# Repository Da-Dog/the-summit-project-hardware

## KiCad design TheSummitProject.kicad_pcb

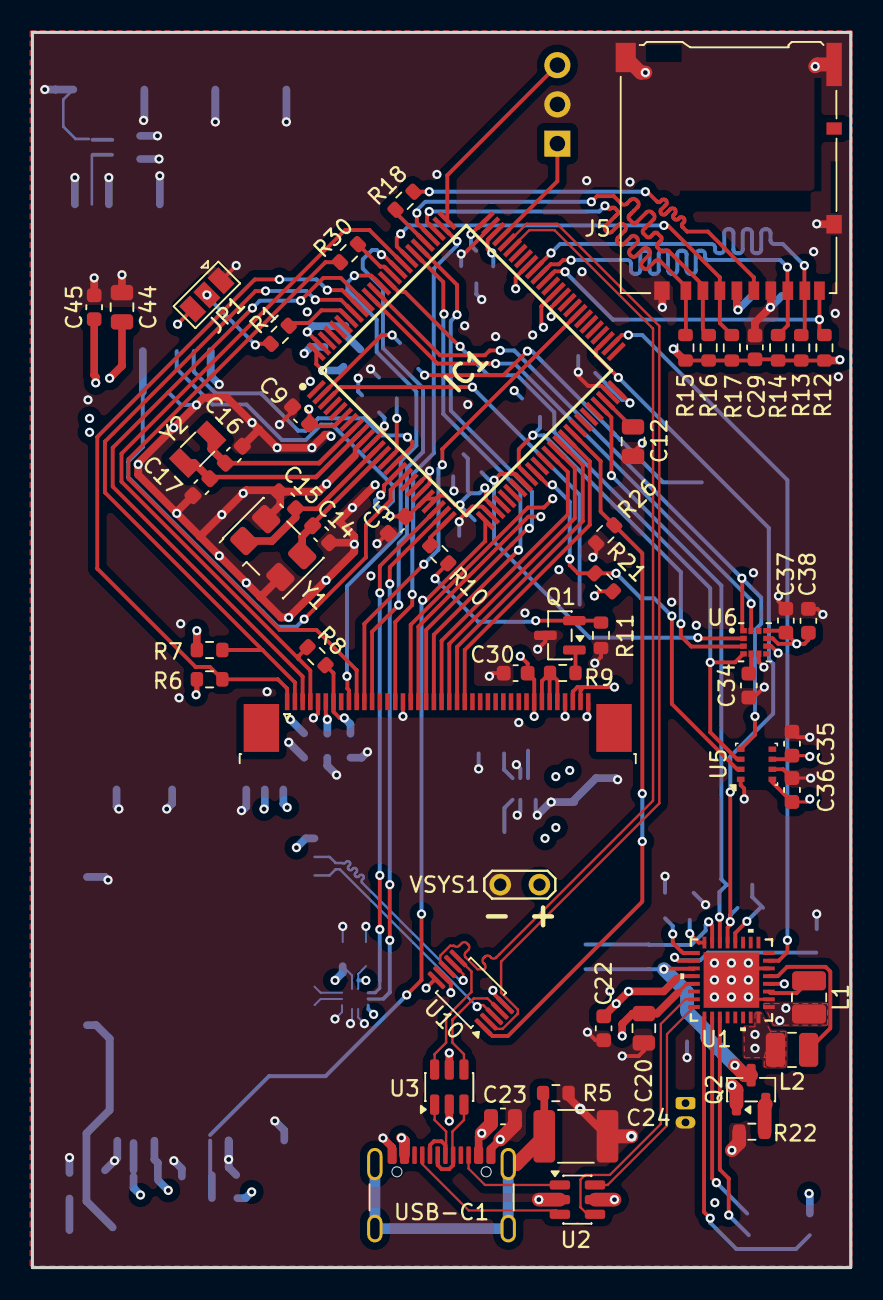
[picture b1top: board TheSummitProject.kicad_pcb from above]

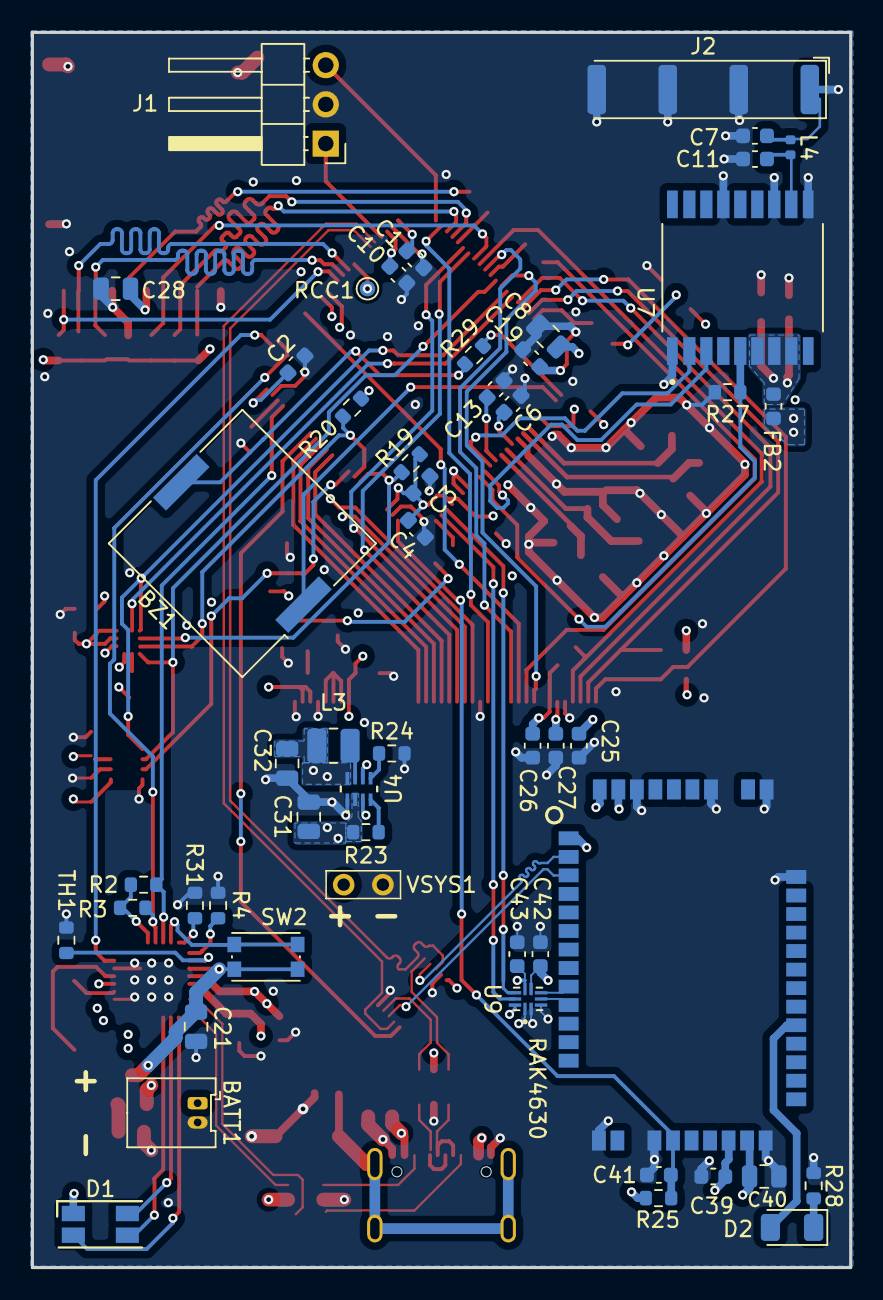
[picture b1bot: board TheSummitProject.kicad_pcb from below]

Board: 6 copper layers, 53.0 x 80.0 mm, 108 parts (51 on the bottom side), 100 nets.

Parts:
BATT1: Battery Connector; Molex_PicoBlade_53048-0210_1x02_P1.25mm_Horizontal
BZ1: PKLCS1212E4001-R1; Buzzer_Murata_PKLCS1212E
C1, C2, C3, C4, C5, C6, C9, C10, C13, C19, C23, C25, C26, C29, C30, C35, C36, C37, C38, C39, C41, C42, C43, C45: 100n; C_0603_1608Metric
C7: X; C_0603_1608Metric
C8, C28, C32, C40, C44: 10u; C_0805_2012Metric
C11: 1.8p; C_0603_1608Metric
C12, C20, C21, C31: 4.7u; C_0805_2012Metric
C14, C15: 10p; C_0603_1608Metric
C16, C17: 8p; C_0603_1608Metric
C22: 10u; C_0603_1608Metric
C24: 4.7n; C_1812_4532Metric
C27: 1u; C_0603_1608Metric
C34: 220n; C_0603_1608Metric
D1: PWR_LED; LED_RGB_1210
D2: Blue_LED; LED_1206_3216Metric
FB2: 120R; L_0603_1608Metric
IC1: STM32U5F7VJT6; QFP50P1600X1600X160-100N
J1: JTAG; PinHeader_1x03_P2.54mm_Horizontal
J2: GPS_ANT; Antenova_SR4G013_GPS
J4: Screen FPC; TE_4-1734839-0_1x40-1MP_P0.5mm_Horizontal
J5: Micro_SD_Card_Det1; microSD_HC_Hirose_DM3AT-SF-PEJM5
JP1: SolderJumper_3_Open; SolderJumper-3_P1.3mm_Open_Pad1.0x1.5mm
L1, L2, L3: 2.2u; L_1008_2520Metric
L4: 1.8n; L_0402_1005Metric
Q1: NMOS; SOT-23
Q2: PMOS; SOT-23
R1, R11, R13, R14, R15, R16, R17, R25: 10k; R_0603_1608Metric
R2, R3, R6, R7, R8, R19, R20, R21: 4.7k; R_0603_1608Metric
R4: 47k; R_0603_1608Metric
R5: 1m; R_0603_1608Metric
R9: 3.3; R_0603_1608Metric
R10, R28, R29: 100; R_0603_1608Metric
R12, R22, R23, R24, R26, R27: 100k; R_0603_1608Metric
R18: 22; R_0603_1608Metric
R30: 33; R_0603_1608Metric
R31: 300k; R_0603_1608Metric
RCC1: RCC; TestPoint_Pad_D1.0mm
SW2: PWR_BTN; SW_Push_1P1T_NO_CK_KMR2
TH1: 10k; R_0603_1608Metric
U1: NPM1300-CAAA-R; QFN32_5X5_NOR
U2, U3: USBLC6-2SC6; SOT-23-6
U4: TPS62840DLCR; VSON8_2P1X1P6_TEX
U5: BME280; Bosch_LGA-8_2.5x2.5mm_P0.65mm_ClockwisePinNumbering
U6: LSM303AGR; PQFN50P200X200X100-12N
U7: MAX-M10S-00B; XCVR_MAX-M10S-00B
U8: RAK4630
U9: SN74AVC2T245RSWR; QFN40P180X140X55-10N
U10: TS3USB30EDGSR; TSSOP-10_3x3mm_P0.5mm
USB-C1: USB C; USB_C_Receptacle_GCT_USB4105-xx-A_16P_TopMnt_Horizontal
VSYS1: VSYS; TestPoint_2Pads_Pitch2.54mm_Drill0.8mm
Y1: 16Mhz; Crystal_SMD_5032-4Pin_5.0x3.2mm
Y2: 32.768Khz; Crystal_SMD_3215-2Pin_3.2x1.5mm

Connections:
+1.8V: C1.1, C2.1, C3.1, C4.1, C5.1, C6.1, C8.1, C9.2, C19.1, C25.1, C26.2, C27.1, C35.2, C36.1, C37.2, C38.1, C43.2, FB2.1, IC1.6 (VBAT), IC1.11 (VDD_1), IC1.21 (VREF+), IC1.22 (VDDA), IC1.28 (VDD_2), IC1.50 (VDD_3), IC1.75 (VDD_4), IC1.100 (VDD_5), J4.6, J4.7, J4.38, J4.39, JP1.3 (B), L1.2, R2.2, R3.2, R6.2, R7.2, R8.2, R19.1, R20.1, R21.1, U1.1 (VOUT1), U1.12 (VDDIO), U5.6 (VDDIO), U5.8 (VDD), U6.9 (VDD), U6.10 (VDD_IO), U9.7 (VCCA), U9.10 (DIR1), U10.10 (VCC)
+3.3V: C10.2, C39.1, C40.1, C42.1, D1.1 (A), IC1.73 (VDDUSB), L2.2, R25.1, U1.32 (VOUT2), U8.40 (VBAT_IO_SX), U8.42 (VBAT_SX), U8.44 (VDD_NRF), U9.6 (VCCB)
+3.3V_HP: C28.2, C29.2, C30.2, C32.1, J4.33, J5.4 (VDD), L3.2, R12.1, R13.1, R14.1, R15.2, R16.2, R17.2, U4.8 (VOS)
/MCU/NRST: C13.1, IC1.14 (NRST)
/MCU/STM32+: IC1.71 (USB_OTG_HS_DP), U10.2 (D1+)
/MCU/STM32-: IC1.70 (USB_OTG_HS_DM), U10.8 (D1-)
/MCU/SW_BOOT0: IC1.94 (PH3-BOOT0), R1.2
/MCU/USB+: U3.3 (I/O2), U3.4 (I/O2), U10.4 (D+), USB-C1.A6 (D+), USB-C1.B6 (D+)
/MCU/USB-: U3.1 (I/O1), U3.6 (I/O1), U10.6 (D-), USB-C1.A7 (D-), USB-C1.B7 (D-)
/MCU/USB_SEL: IC1.42 (PE11), R26.1, U10.1 (S)
ACC_INT: IC1.90 (ACC_INT), U6.12 (INT_1_XL)
BME280_CS: IC1.35 (BME280_CS), R21.2, U5.2 (CSB)
CC1: U1.23 (CC1), U2.4 (I/O2)
CC2: U1.24 (CC2), U2.6 (I/O1)
CTP_INT: IC1.84 (CTP_INT), J4.4, R8.1
CTP_RST: IC1.91 (CTP_RST), J4.3
CTP_SCL: IC1.92 (CTP_SCL), J4.1, R6.1
CTP_SDA: IC1.93 (CTP_SDA), J4.2, R7.1
GND: BATT1.2, C1.2, C2.2, C3.2, C4.2, C5.2, C6.2, C7.2, C8.2, C9.1, C10.1, C11.2, C12.1, C13.2, C14.1, C15.1, C16.1, C17.1, C19.2, C20.1, C21.1, C22.2, C23.2, C24.2, C25.2, C26.1, C27.2, C28.1, C29.1, C30.1, C31.1, C32.2, C34.1, C35.1, C36.2, C37.1, C38.2, C39.2, C40.2, C41.2, C42.2, C43.1, C44.1, C45.2, IC1.10 (VSS_1), IC1.19 (VSSA), IC1.20 (VREF-), IC1.27 (VSS_2), IC1.49 (VSS_3), IC1.74 (VSS_4), IC1.99 (VSS_5), J1.2, J2.2 (Ext), J4.5, J4.16, J4.37, J4.40, J5.6 (VSS), J5.SH (SHIELD), JP1.1 (A), Q1.3 (S), R4.1, R5.1, R11.2, R22.2, R24.2, R26.2, R27.2, R28.2, R31.2, TH1.1, U1.2 (PVSS1), U1.6 (PVSS2), U1.33 (AVSS), U2.2 (GND), U3.2 (GND), U4.1 (GND), U4.3 (MODE), U4.6 (STOP), U5.1 (GND), U5.7 (GND), U6.6 (GND), U6.8 (GND), U7.1 (GND), U7.10 (GND), U7.12 (GND), U7.15 (VIO_SEL), U8.1 (GND), U8.2 (GND1), U8.3 (GND2), U8.4 (GND3), U8.5 (GND4), U8.6 (GND5), U8.7 (GND6), U9.1 (DIR2), U9.2 (~OE), U9.3 (GND), U10.5 (GND), U10.9 (~OE), USB-C1.A1 (GND), USB-C1.A12 (GND), USB-C1.B1 (GND), USB-C1.B12 (GND), VSYS1.2, Y1.2 (G), Y1.4 (G)
GPS_INT: IC1.17 (GPS_INT), R27.1, U7.5 (EXTINT)
GPS_RX: IC1.15 (GPS_RX), U7.2 (TXD)
GPS_TX: IC1.16 (GPS_TX), U7.3 (RXD)
LCD_D0: IC1.61 (LCD_D0), J4.17
LCD_D1: IC1.62 (LCD_D1), J4.18
LCD_D2: IC1.81 (LCD_D2), J4.19
LCD_D3: IC1.82 (LCD_D3), J4.20
LCD_D4: IC1.38 (LCD_D4), J4.21
LCD_D5: IC1.39 (LCD_D5), J4.22
LCD_D6: IC1.40 (LCD_D6), J4.23
LCD_D7: IC1.41 (LCD_D7), J4.24
LCD_NE1: IC1.88 (LCD_NE1), J4.9
LCD_NOE: IC1.85 (LCD_NOE), J4.12
LCD_NWE: IC1.86 (LCD_NWE), R30.2
LCD_PWM: IC1.25 (BPR), R10.1
LCD_RS: IC1.58 (LCD_RS), J4.11
LCD_RST: IC1.77 (LCD_RST), J4.15
LSM303_MAG_CS: IC1.34 (LSM303_MAG_CS), R20.2, U6.3 (CS_MAG)
LSM303_XL_CS: IC1.33 (LSM303_XL_CS), R19.2, U6.2 (CS_XL)
LoRA+: U8.38 (USB+), U10.3 (D2+)
LoRA-: U8.39 (USB-), U10.7 (D2-)
LoRa_RX: IC1.24 (LoRa_RX), U9.9 (A2)
LoRa_TX: IC1.23 (LoRa_TX), U9.8 (A1)
NPM_INT: IC1.52 (NPM_INT), U1.7 (GPIO0)
NRF_RST: C41.1, IC1.26 (NRF_RST), R25.2, U8.8 (NRF_RESET)
unnamed: BATT1.1, Q2.1 (D)
unnamed: BZ1.2 (-), R29.2
unnamed: D1.3 (BK), U1.27 (LED2)
unnamed: D1.4 (GK), U1.26 (LED1)
unnamed: D1.2 (RK), U1.25 (LED0)
unnamed: D2.2 (A), U8.32 (P1.03/LED1)
unnamed: D2.1 (K), R28.1
unnamed: IC1.76 (DEBUG_JTCK-SWCLK), J1.3
unnamed: IC1.72 (DEBUG_JTMS-SWDIO), J1.1
unnamed: C15.2, IC1.12 (HSE_IN), Y1.1
unnamed: C14.2, IC1.13 (HSE_OUT), Y1.3
unnamed: C16.2, IC1.8 (LSE_IN), Y2.1
unnamed: C17.2, IC1.9 (LSE_OUT), Y2.2
unnamed: C12.2, IC1.48 (VCAP)
unnamed: C7.1, J2.1 (In), L4.1
unnamed: J4.10, R30.1
unnamed: J4.34, J4.35, J4.36, R9.1
unnamed: J5.5 (CLK), R18.1
unnamed: JP1.2 (C), R1.1
unnamed: Q1.1 (D), R9.2
unnamed: Q1.2 (G), R10.2, R11.1
unnamed: Q2.2 (G), R22.1
unnamed: TH1.2, U1.18 (NTC)
unnamed: SW2.1, U1.15 (SHPHLD)
unnamed: L1.1, U1.3 (SW1)
unnamed: L2.1, U1.5 (SW2)
unnamed: R4.2, U1.17 (VSET1)
unnamed: R31.1, U1.16 (VSET2)
unnamed: R23.1, U4.4 (EN)
unnamed: L3.1, U4.7 (SW)
unnamed: R24.1, U4.5 (VSET)
unnamed: C34.2, U6.5 (C1)
unnamed: C11.1, L4.2, U7.11 (RF_IN)
unnamed: C44.2, C45.1, FB2.2, U7.6 (V_BCKP), U7.7 (V_IO), U7.8 (VCC)
unnamed: U8.20 (P0.19/UART1_RX), U9.5 (B1)
unnamed: U8.21 (P0.20/UART1_TX), U9.4 (B2)
unnamed: U2.3 (I/O2), USB-C1.A5 (CC1)
unnamed: U2.1 (I/O1), USB-C1.B5 (CC2)
unnamed: C24.1, R5.2, USB-C1.SH (SHIELD)
PIEZO_P1: BZ1.1 (+), IC1.3 (PIEZO_P2)
PIEZO_P2: IC1.2 (PIEZO_P1), R29.1
PM_SCL: IC1.47 (PM_SCL), R2.1, U1.14 (SCL)
PM_SDA: IC1.53 (PM_SDA), R3.1, U1.13 (SDA)
RCC_MCO: IC1.67 (RCC_MCO), RCC1.1 (Pin_1_1)
SD_CK: IC1.80 (SD_CK), R18.2
SD_CMD: IC1.83 (SD_CMD), J5.3 (CMD), R17.1
SD_D0: IC1.65 (SD_D0), J5.7 (DAT0), R14.2
SD_D1: IC1.66 (SD_D1), J5.8 (DAT1), R13.2
SD_D2: IC1.78 (SD_D2), J5.1 (DAT2), R15.1
SD_D3: IC1.79 (SD_D3), J5.2 (DAT3/CD), R16.1
SD_DETECT: IC1.64 (SD_DETECT), J5.9 (DET), R12.2
SNSR_MOSI: IC1.87 (SNSR_MOSI), U5.3 (SDI), U6.4 (SDA/SDI/SDO)
SNSR_SCK: IC1.89 (SNSR_SCK), U5.4 (SCK), U6.1 (SCL/SPC)
VBAT: C21.2, Q2.3 (S), SW2.2, U1.19 (VBAT)
VBUS: C20.2, C23.1, U1.21 (VBUS), U2.5 (VBUS), U3.5 (VBUS), U8.43 (VBUS), USB-C1.A4 (VBUS), USB-C1.A9 (VBUS), USB-C1.B4 (VBUS), USB-C1.B9 (VBUS)
VSYS: C22.1, C31.2, R23.2, U1.4 (PVDD), U1.20 (VSYS), U4.2 (VIN), U8.41 (VBAT_NRF), VSYS1.1
